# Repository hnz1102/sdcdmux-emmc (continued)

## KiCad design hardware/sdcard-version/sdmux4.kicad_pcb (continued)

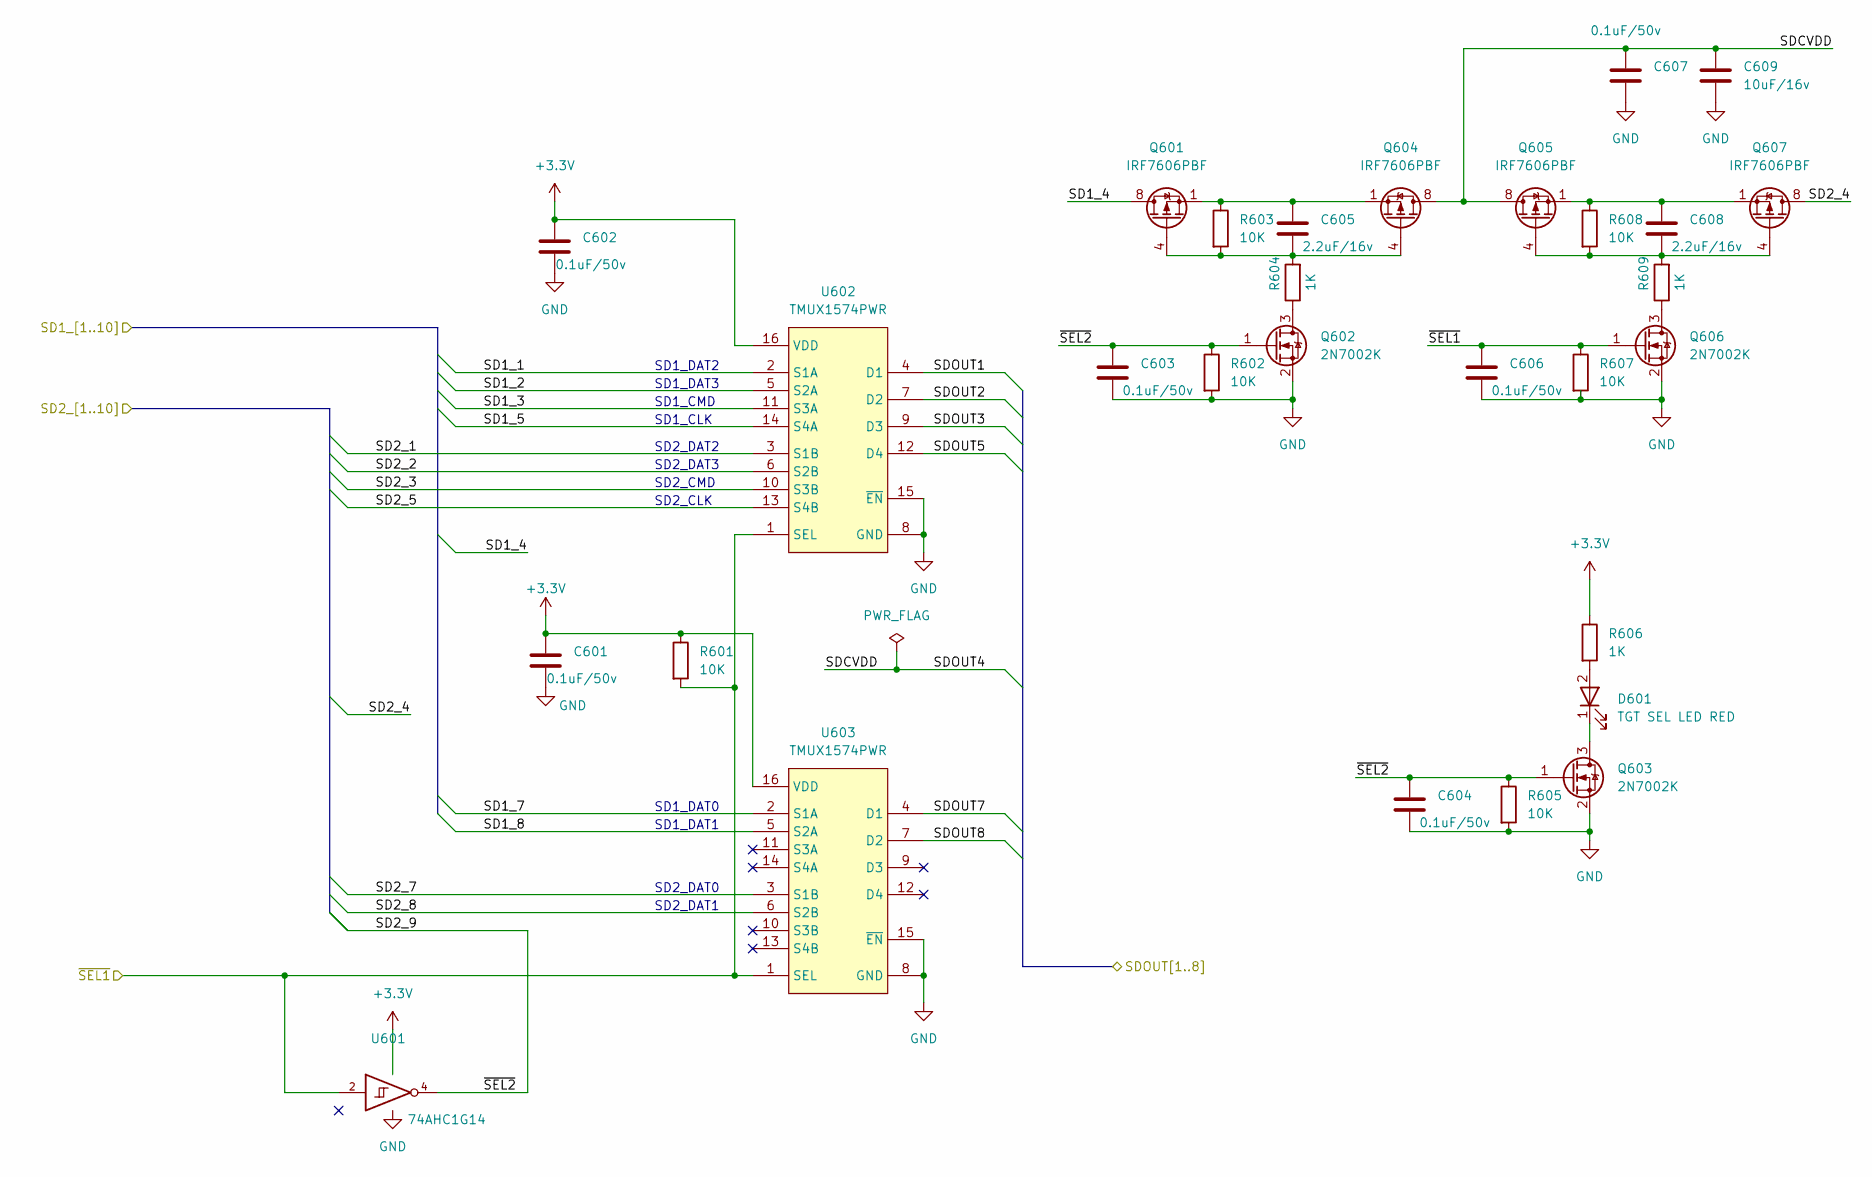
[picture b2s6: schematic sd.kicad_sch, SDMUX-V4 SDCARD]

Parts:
C601, C602, C603, C604, C606, C607: 0.1uF/50v; C_0603_1608Metric_Pad1.08x0.95mm_HandSolder
C605, C608: 2.2uF/16v; C_0603_1608Metric_Pad1.08x0.95mm_HandSolder
C609: 10uF/16v; C_0805_2012Metric_Pad1.18x1.45mm_HandSolder
D601: TGT SEL LED RED; LED_0603_1608Metric_Pad1.05x0.95mm_HandSolder
Q601, Q604, Q605, Q607: IRF7606PBF; MSOP-8_3x3mm_P0.65mm
Q602, Q603, Q606: 2N7002K; SOT-23
R601, R602, R603, R605, R607, R608: 10K; R_0805_2012Metric_Pad1.20x1.40mm_HandSolder
R604, R606, R609: 1K; R_0805_2012Metric_Pad1.20x1.40mm_HandSolder
U601: 74AHC1G14; SOT-23-5_HandSoldering
U602, U603: TMUX1574PWR; TSSOP-16_4.4x5mm_P0.65mm

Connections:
+3.3V: C601.1, C602.1, R601.1, R606.1, U601.5 (VCC), U602.16 (VDD), U603.16 (VDD); also elsewhere on the board
/SDCARD_READER/SD1: U602.3 (S1B); also elsewhere on the board
/SDCARD_READER/SD2: U602.6 (S2B); also elsewhere on the board
/SDCARD_READER/SD3: U602.10 (S3B); also elsewhere on the board
/SDCARD_READER/SD4: Q607.5 (D), Q607.6 (D), Q607.7 (D), Q607.8 (D); also elsewhere on the board
/SDCARD_READER/SD5: U602.13 (S4B); also elsewhere on the board
/SDCARD_READER/SD7: U603.3 (S1B); also elsewhere on the board
/SDCARD_READER/SD8: U603.6 (S2B); also elsewhere on the board
/SDCARD_READER/SD9: C603.1, C604.1, Q602.1 (G), Q603.1 (G), R602.1, R605.1, U601.4; also elsewhere on the board
/SDMUX/SD1_1: U602.2 (S1A); also elsewhere on the board
/SDMUX/SD1_2: U602.5 (S2A); also elsewhere on the board
/SDMUX/SD1_3: U602.11 (S3A); also elsewhere on the board
/SDMUX/SD1_4: Q601.5 (D), Q601.6 (D), Q601.7 (D), Q601.8 (D); also elsewhere on the board
/SDMUX/SD1_5: U602.14 (S4A); also elsewhere on the board
/SDMUX/SD1_7: U603.2 (S1A); also elsewhere on the board
/SDMUX/SD1_8: U603.5 (S2A); also elsewhere on the board
/SDMUX/SDOUT1: U602.4 (D1); also elsewhere on the board
/SDMUX/SDOUT2: U602.7 (D2); also elsewhere on the board
/SDMUX/SDOUT3: U602.9 (D3); also elsewhere on the board
/SDMUX/SDOUT4: C607.1, C609.1, Q604.5 (D), Q604.6 (D), Q604.7 (D), Q604.8 (D), Q605.5 (D), Q605.6 (D), Q605.7 (D), Q605.8 (D); also elsewhere on the board
/SDMUX/SDOUT5: U602.12 (D4); also elsewhere on the board
/SDMUX/SDOUT7: U603.4 (D1); also elsewhere on the board
/SDMUX/SDOUT8: U603.7 (D2); also elsewhere on the board
/SDMUX/~SEL1: C606.1, Q606.1 (G), R601.2, R607.1, U601.2, U602.1 (SEL), U603.1 (SEL); also elsewhere on the board
GND: C601.2, C602.2, C603.2, C604.2, C606.2, C607.2, C609.2, Q602.2 (S), Q603.2 (S), Q606.2 (S), R602.2, R605.2, R607.2, U601.3 (GND), U602.8 (GND), U602.15 (~EN), U603.8 (GND), U603.15 (~EN); also elsewhere on the board
unnamed: C605.1, Q601.1 (S), Q601.2 (S), Q601.3 (S), Q604.1 (S), Q604.2 (S), Q604.3 (S), R603.1
unnamed: C608.1, Q605.1 (S), Q605.2 (S), Q605.3 (S), Q607.1 (S), Q607.2 (S), Q607.3 (S), R608.1
unnamed: D601.2 (A), R606.2
unnamed: D601.1 (K), Q603.3 (D)
unnamed: C605.2, Q601.4 (G), Q604.4 (G), R603.2, R604.2
unnamed: Q602.3 (D), R604.1
unnamed: C608.2, Q605.4 (G), Q607.4 (G), R608.2, R609.2
unnamed: Q606.3 (D), R609.1

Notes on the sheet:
SD1_DAT3
SD2_DAT3
SD1_DAT1
SD2_DAT1
SD2_CLK
SD1_CLK
SD2_DAT0
SD2_DAT2
SD1_DAT2
SD1_DAT0
SD2_CMD
SD1_CMD

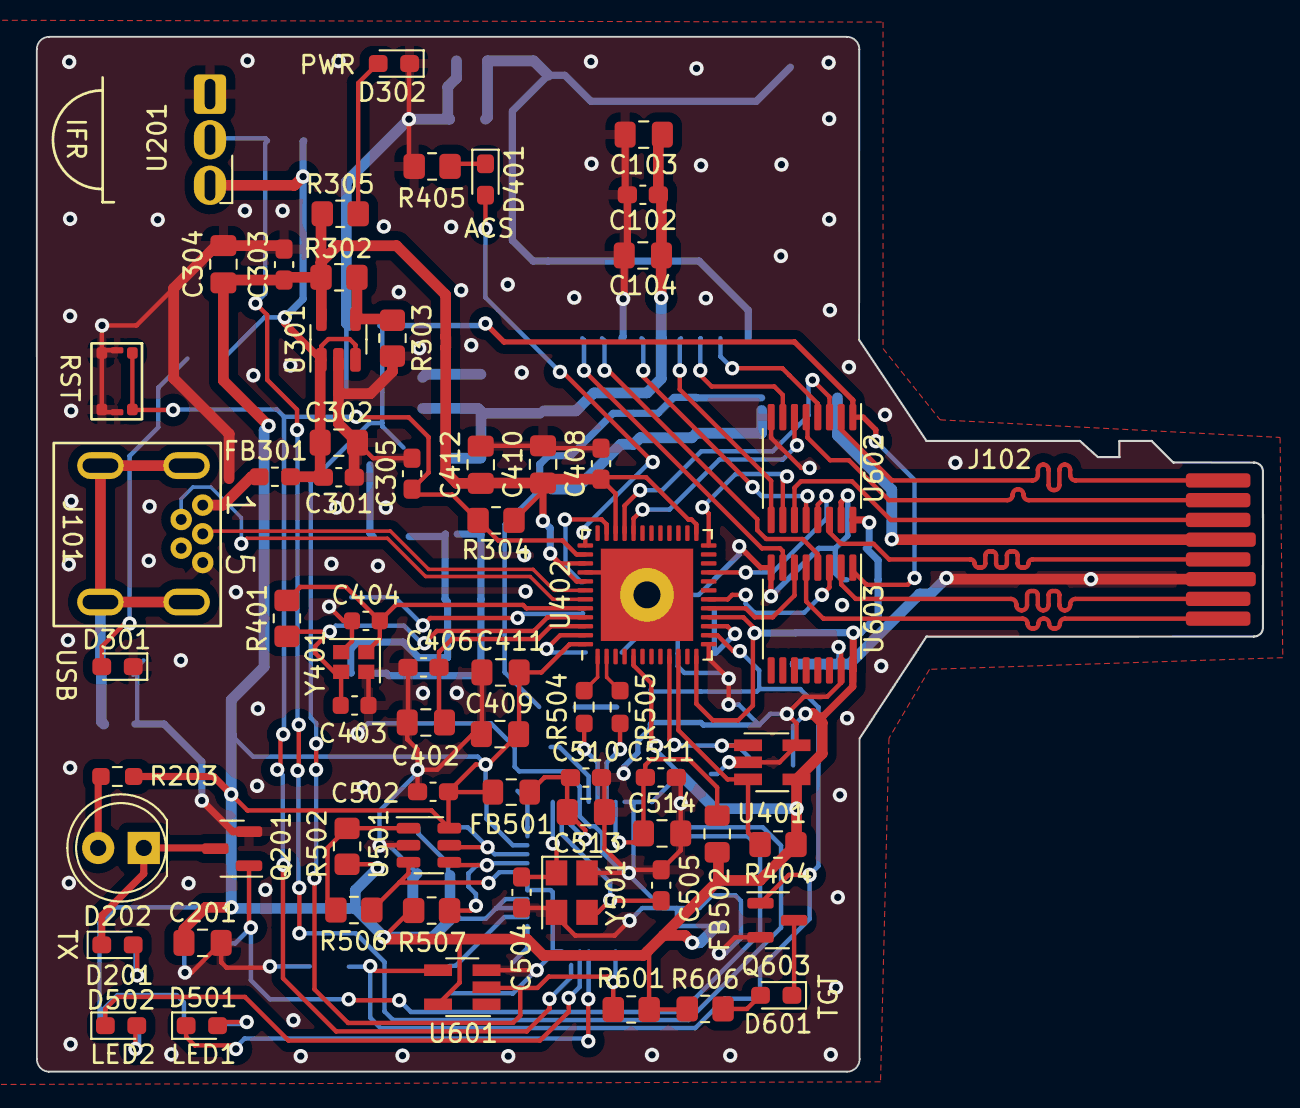
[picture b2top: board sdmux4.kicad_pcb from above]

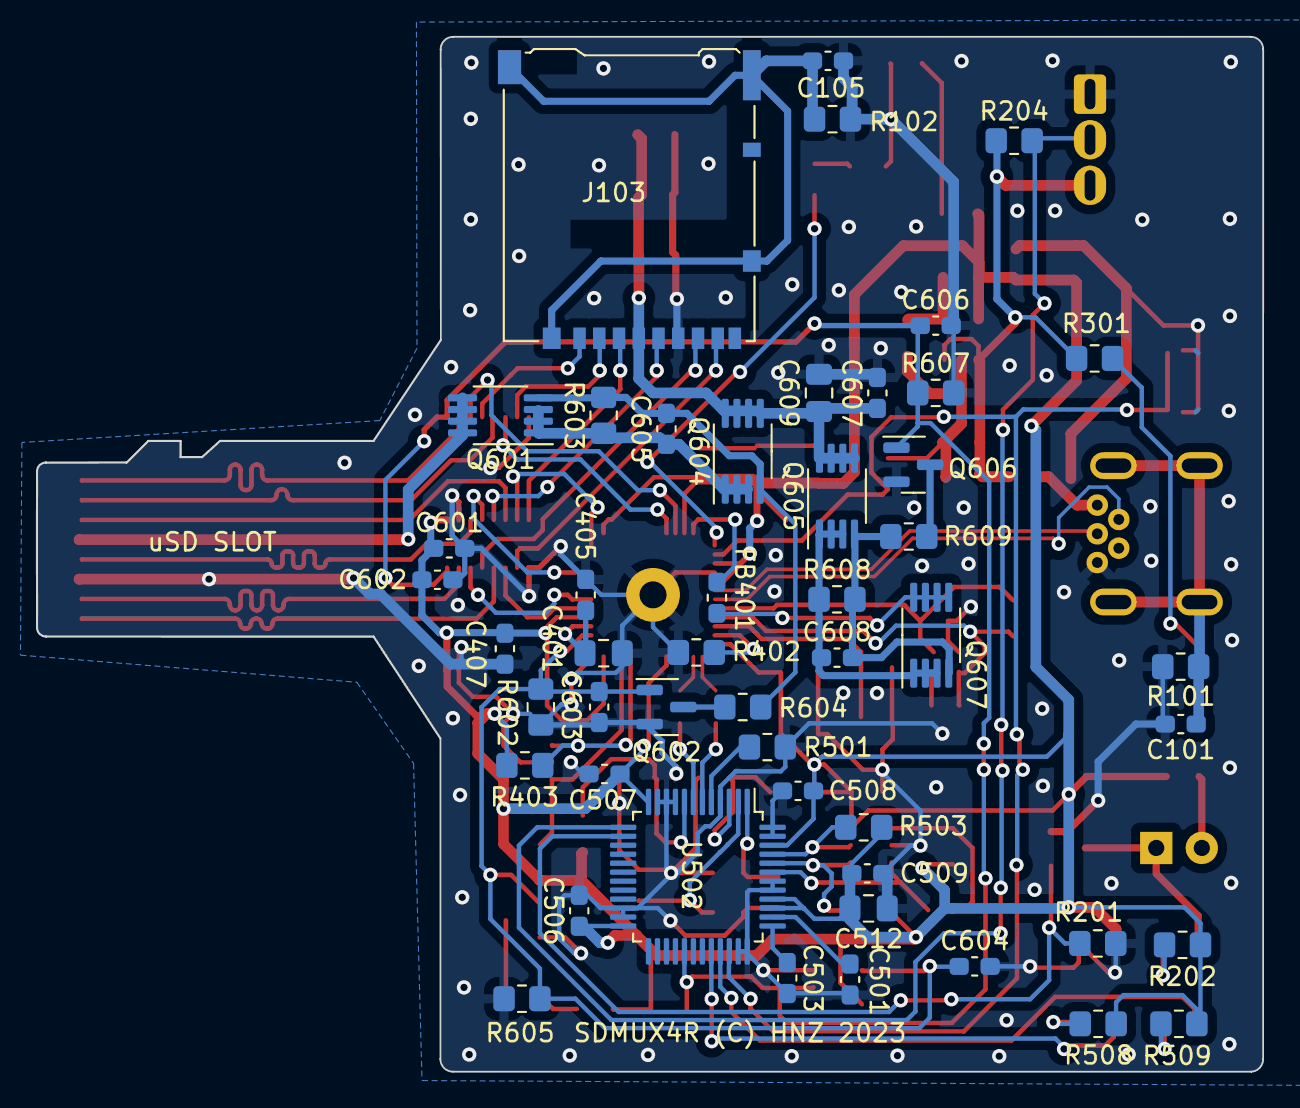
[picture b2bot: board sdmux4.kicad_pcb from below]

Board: 2 copper layers, 68.3 x 57.7 mm, 115 parts (49 on the bottom side), 77 nets.

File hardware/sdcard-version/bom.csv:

designator,quantity,value,pack,mpn,mount_type
"C101, C102, C105, C301, C303, C305, C405, C406, C407, C408, C501, C502, C503, C506, C507, C508, C509, C510, C511, C601, C602, C603, C604, C606, C607",25,0.1uF/50v,C_0603_1608Metric_Pad1.08x0.95mm_HandSolder,,smt
"C103, C401, C402, C409, C410",5,1uF/10v,C_0805_2012Metric_Pad1.18x1.45mm_HandSolder,,smt
"C104, C411, C412, C512, C513, C514",6,4.7uF/50v,C_0805_2012Metric_Pad1.18x1.45mm_HandSolder,,smt
"C201, C302, C304, C609",4,10uF/16v,C_0805_2012Metric_Pad1.18x1.45mm_HandSolder,,smt
"C403, C404",2,27pF/50v,C_0603_1608Metric,,smt
"C504, C505",2,27pF/50v,C_0603_1608Metric_Pad1.08x0.95mm_HandSolder,,smt
"C605, C608",2,2.2uF/16v,C_0603_1608Metric_Pad1.08x0.95mm_HandSolder,,smt
"D201, D301, D302, D401",4,LED RED,LED_0603_1608Metric_Pad1.05x0.95mm_HandSolder,,smt
D202,1,OSI5LA5113A,LED_D5.0mm,,tht
D501,1,IND-1 LED GRN,LED_0603_1608Metric_Pad1.05x0.95mm_HandSolder,,smt
D502,1,IND-2 LED GRN,LED_0603_1608Metric_Pad1.05x0.95mm_HandSolder,,smt
D601,1,TGT SEL LED RED,LED_0603_1608Metric_Pad1.05x0.95mm_HandSolder,,smt
FB301,1,BK2125HS601-T,L_0603_1608Metric_Pad1.05x0.95mm_HandSolder,,smt
FB401,1,BLM18RK102SN1,L_0603_1608Metric_Pad1.05x0.95mm_HandSolder,,smt
"FB501, FB502",2,BK2125HS601-T,L_0805_2012Metric_Pad1.15x1.40mm_HandSolder,,smt
J101,1,USB_B_Mini,usb mini B connector c2235 dim 2,,tht
J102,1,uSD-CARD-PAD,uSD Card Pad,,smt
J103,1,Micro_SD_Card_Det_Hirose_DM3AT-SF-PEJM5,microSD_HC_Hirose_DM3AT-SF-PEJM5,,smt
"Q201, Q602, Q603, Q606",4,2N7002K,SOT-23,,smt
"Q601, Q604, Q605, Q607",4,IRF7606PBF,MSOP-8_3x3mm_P0.65mm,,smt
"R101, R102, R201, R204, R304, R403, R404, R502, R503, R507, R601, R602, R603, R605, R607, R608",16,10K,R_0805_2012Metric_Pad1.20x1.40mm_HandSolder,,smt
"R202, R301, R604, R606, R609",5,1K,R_0805_2012Metric_Pad1.20x1.40mm_HandSolder,,smt
R203,1,33R,R_0603_1608Metric_Pad0.98x0.95mm_HandSolder,,smt
R302,1,20K 1%,R_0805_2012Metric_Pad1.20x1.40mm_HandSolder,,smt
"R303, R402, R501",3,12K 1%,R_0805_2012Metric_Pad1.20x1.40mm_HandSolder,,smt
R305,1,330,R_0805_2012Metric_Pad1.20x1.40mm_HandSolder,,smt
R401,1,1M,R_0805_2012Metric_Pad1.20x1.40mm_HandSolder,,smt
R405,1,330R,R_0805_2012Metric_Pad1.20x1.40mm_HandSolder,,smt
"R504, R505",2,27R,R_0603_1608Metric_Pad0.98x0.95mm_HandSolder,,smt
R506,1,2K,R_0805_2012Metric_Pad1.20x1.40mm_HandSolder,,smt
"R508, R509",2,220,R_0805_2012Metric_Pad1.20x1.40mm_HandSolder,,smt
SW301,1,RESET SW,WS-TASV SMT Tact Switch,,smt
U201,1,SPS-445,SPS445 3pin,,tht
U301,1,SPX3819M5-L,SOT-23-5,,smt
U401,1,AT24MAC402-STUM,SOT-23-5_HandSoldering,,smt
U402,1,USB2640-HZH-02,QFN-48-1EP_7x7mm_P0.5mm_EP5.15x5.15mm,,smt
U501,1,93LCxxBxxOT,SOT-23-6,,smt
U502,1,FT232HL,LQFP-48_7x7mm_P0.5mm,,smt
U601,1,74AHC1G14,SOT-23-5_HandSoldering,,smt
"U602, U603",2,TMUX1574PWR,TSSOP-16_4.4x5mm_P0.65mm,,smt
Y401,1,24MHz,Crystal_SMD_2016-4Pin_2.0x1.6mm,,smt
Y501,1,12MHz,Crystal_SMD_3225-4Pin_3.2x2.5mm,,smt

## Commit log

2023-07-12 Add movie in the README
2023-07-16 Add SD-CARD version schematics
2023-07-20 Using the libftdi driver instead of libftd2xx.
2023-07-21 Fiexd typo
2023-07-22 Change transmit baudrate.
2023-08-05 Update BOM list
2023-08-14 Added USB type-C version
2023-08-15 Update BOM for type-c version
2023-08-15 Update photo
2023-08-19 Add case for type-c version
2023-08-20 Update front photo.
2023-08-25 Add udev rules
2024-05-09 Corrected part number in the BOM
